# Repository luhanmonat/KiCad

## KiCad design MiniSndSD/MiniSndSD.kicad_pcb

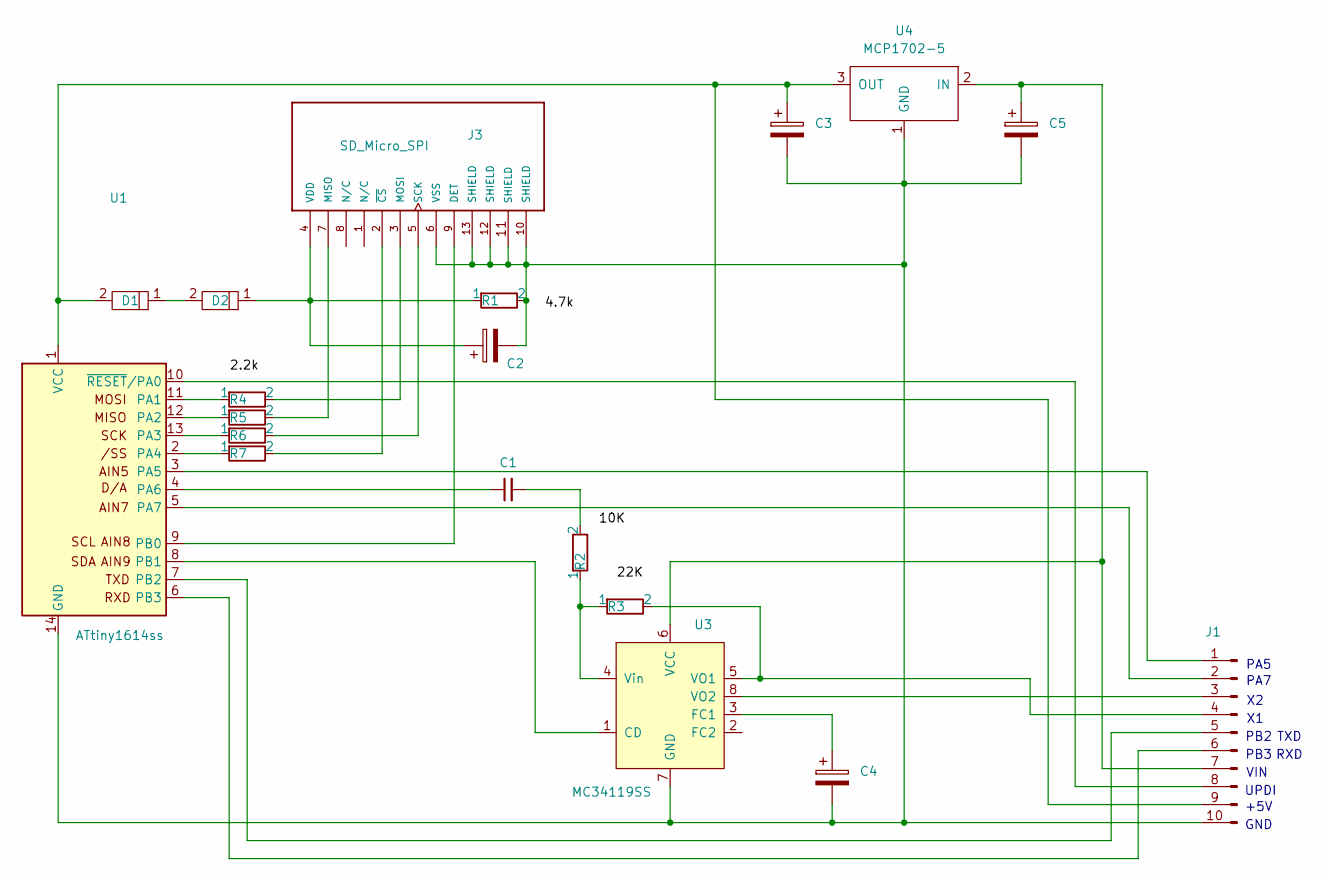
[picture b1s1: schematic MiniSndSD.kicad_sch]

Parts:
C1: C_Disc; C_Disc1
C2, C3, C4, C5: CP_Small; CP_Radial_D4.0mm_P2.00mm
D1, D2: 1N4004; DO_PWR
J1: Conn_01x10_MaleP; PinHeader_1x10_P2.54mm_Vertical
J3: SD_Micro_SPI; SD_Micro4A
R1, R2, R3, R4, R5, R6, R7: Resistor; QWSlim
U1: ATtiny1614ss; SOIC-14_3.9x8.7mm_P1.27mm
U3: MC34119SS; SOIC-8_3.9x4.9mm_P1.27mm
U4: MCP1702-5; TO-92X

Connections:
unnamed: C1.2, R2.2
unnamed: D1.1, D2.2
unnamed: J1.1, U1.3 (PA5)
unnamed: J1.2, U1.5 (PA7)
unnamed: J1.3, U3.8 (VO2)
unnamed: J1.4, R3.2, U3.5 (VO1)
unnamed: J1.5, U1.7 (PB2)
unnamed: J1.6, U1.6 (PB3)
unnamed: C5.1, J1.7, U3.6 (VCC), U4.2 (IN)
unnamed: J1.8, U1.10 (~RESET/PA0)
unnamed: C3.1, D1.2, J1.9, U1.1 (VCC), U4.3 (OUT)
unnamed: C2.2, C3.2, C4.2, C5.2, J1.10, J3.6 (VSS), J3.10 (SHIELD), J3.11 (SHIELD), J3.12 (SHIELD), J3.13 (SHIELD), R1.2, U1.14 (GND), U3.7 (GND), U4.1 (GND)
unnamed: J3.9 (DET), U1.9 (PB0)
unnamed: J3.7 (MISO), R5.2
unnamed: J3.3 (MOSI), R4.2
unnamed: J3.5 (SCK), R6.2
unnamed: C2.1, D2.1, J3.4 (VDD), R1.1
unnamed: J3.2 (~CS), R7.2
unnamed: R4.1, U1.11 (PA1)
unnamed: R5.1, U1.12 (PA2)
unnamed: R6.1, U1.13 (PA3)
unnamed: R7.1, U1.2 (PA4)
unnamed: C1.1, U1.4 (PA6)
unnamed: U1.8 (PB1), U3.1 (CD)
unnamed: C4.1, U3.3 (FC1)
unnamed: R2.1, R3.1, U3.4 (Vin)

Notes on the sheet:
RXD
PA7
PB2
TXD
UPDI
GND
+5V
PB3
PA5
VIN

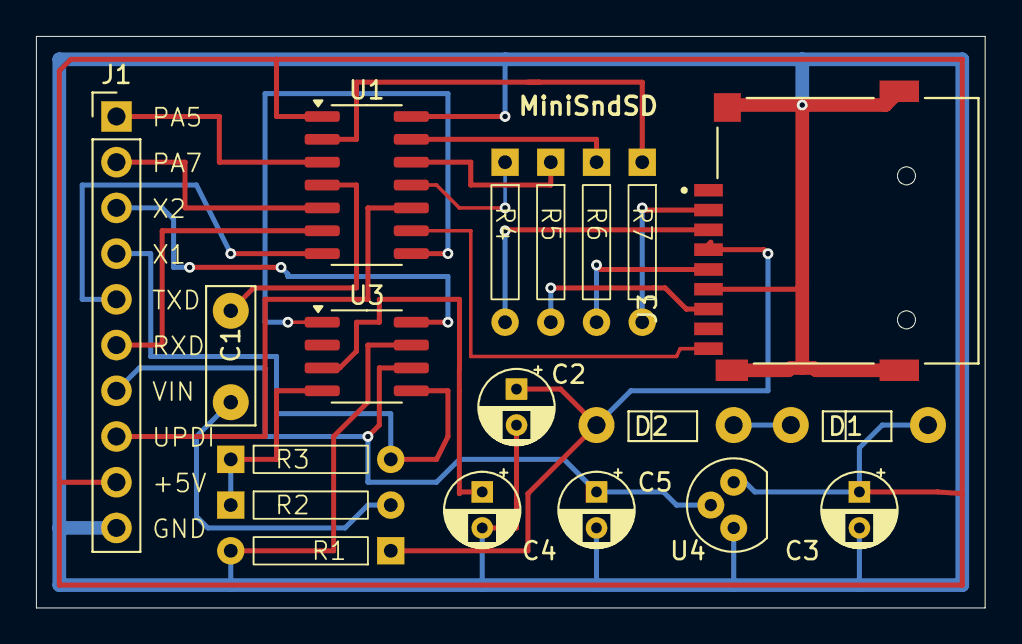
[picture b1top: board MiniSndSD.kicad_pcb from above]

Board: 2 copper layers, 52.7 x 31.7 mm, 19 parts (0 on the bottom side), 26 nets.

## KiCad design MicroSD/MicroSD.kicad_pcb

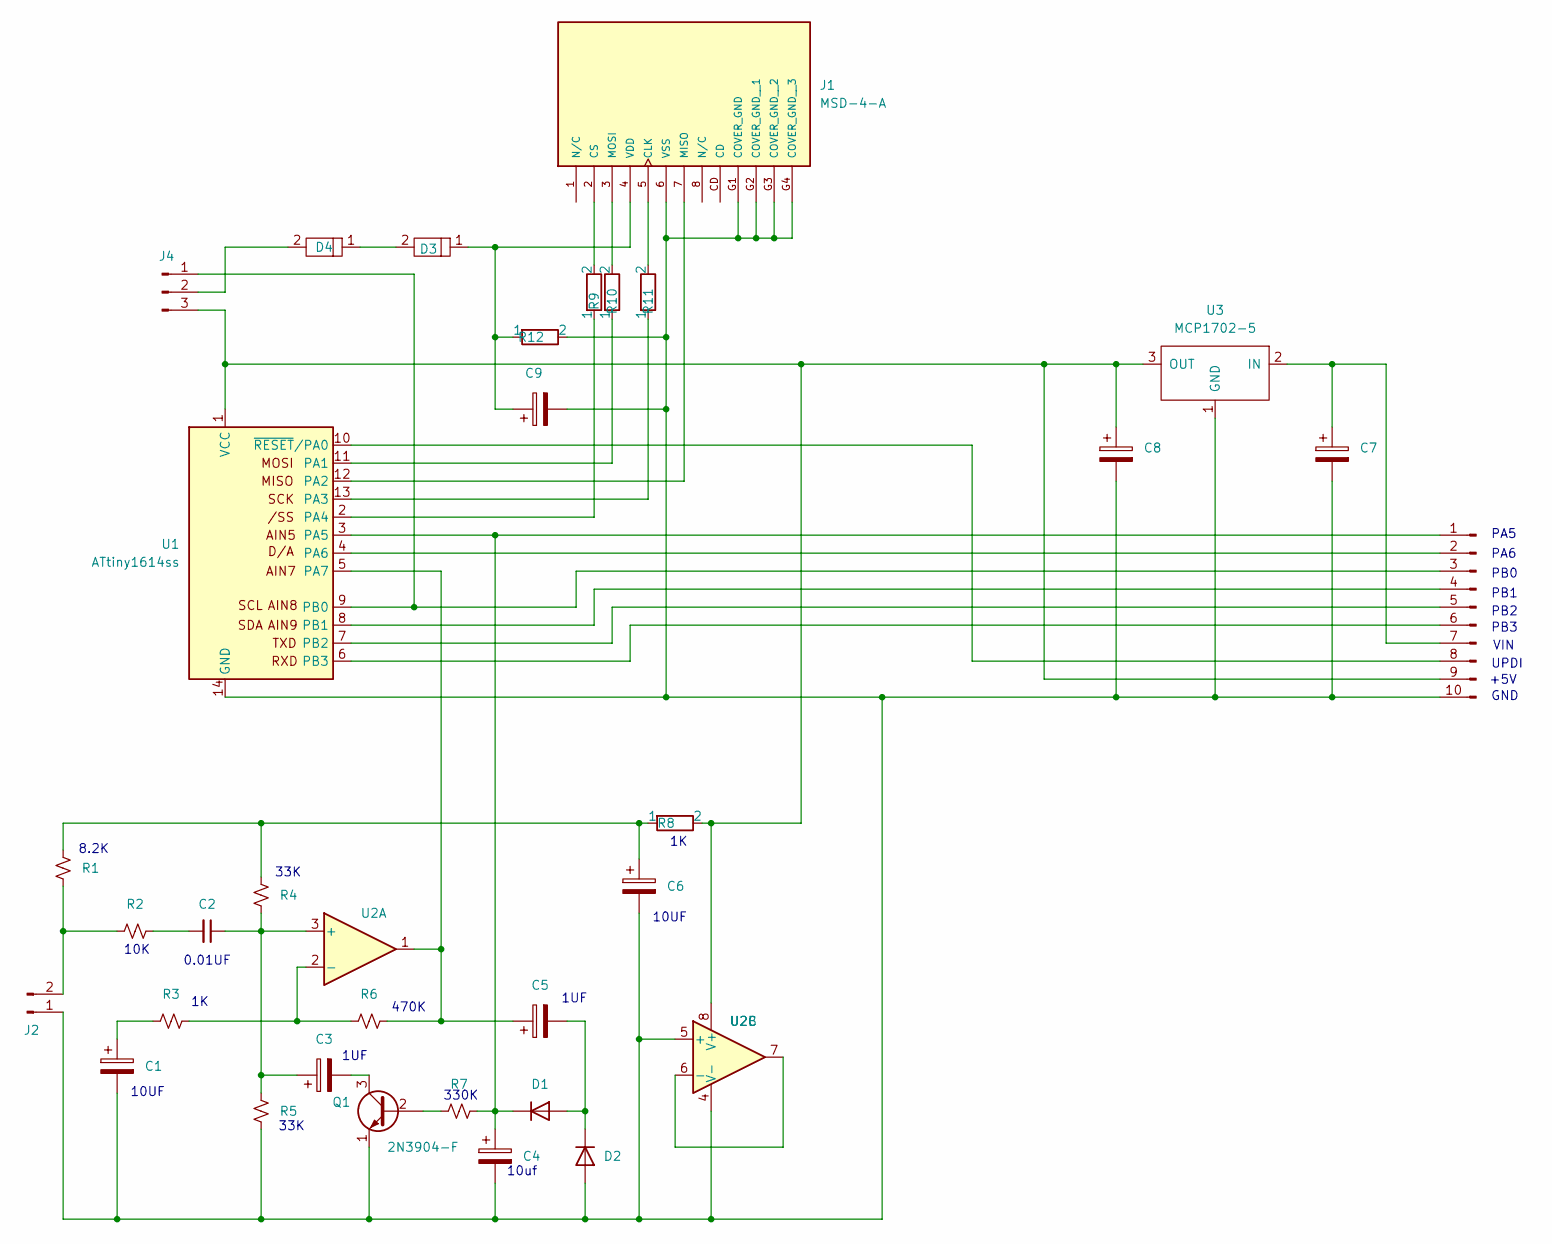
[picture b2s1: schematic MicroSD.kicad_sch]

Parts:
C1, C3, C4, C5, C6, C7, C8, C9: CP_Small; CP_Radial_D4.0mm_P2.00mm
C2: C_Disc; C_Disc1
D1, D2: 1N914; D_DO-35_SOD27_P7.62mm_Horizontal
D3, D4: 1N4004; DO_PWR
J1: MSD-4-A; CUI_MSD-4-A; PARTREV 1.0
J2: Conn_01x02_MH; PinHeader_1x02_P2.54mm_Horizontal
J3: Conn_01x10_MalePH; PinHeader_1x10_P2.54mm_Horizontal
J4: Conn_01x03_Pin; PinHeader_1x03_P2.54mm_Vertical
Q1: 2N3904-F; TO-92L_HandSolder
R1, R2, R3, R4, R5, R6, R7: R_Small; R_Qwatt
R8, R9, R10, R11, R12: Resistor; QWSlim
U1: ATtiny1614ss; SOIC-14_3.9x8.7mm_P1.27mm
U2: OpAmpDual; DIP-8_W7.62mm
U3: MCP1702-5; TO-92X

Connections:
unnamed: C1.1, R3.2
unnamed: C2.2, R2.1
unnamed: C6.1, R1.1, R4.1, R8.1
unnamed: C5.2, D1.2 (A), D2.1 (K)
unnamed: C4.1, D1.1 (K), J3.1, R7.1, U1.3 (PA5)
unnamed: C1.2, C4.2, C6.2, C7.2, C8.2, C9.2, D2.2 (A), J1.6 (VSS), J1.G1 (COVER_GND), J1.G2 (COVER_GND__1), J1.G3 (COVER_GND__2), J1.G4 (COVER_GND__3), J2.1, J3.10, Q1.1 (E), R5.2, R12.2, U1.14 (GND), U2.4 (V-), U2.5 (+), U3.1 (GND)
unnamed: D3.2, D4.1
unnamed: J1.5 (CLK), R11.2
unnamed: J1.2 (CS), R9.2
unnamed: J1.7 (MISO), U1.12 (PA2)
unnamed: J1.3 (MOSI), R10.2
unnamed: C9.1, D3.1, J1.4 (VDD), R12.1
unnamed: J2.2, R1.2, R2.2
unnamed: J3.2, U1.4 (PA6)
unnamed: J3.3, J4.1, U1.9 (PB0)
unnamed: J3.4, U1.8 (PB1)
unnamed: J3.5, U1.7 (PB2)
unnamed: J3.6, U1.6 (PB3)
unnamed: C7.1, J3.7, U3.2 (IN)
unnamed: J3.8, U1.10 (~RESET/PA0)
unnamed: C8.1, J3.9, J4.3, R8.2, U1.1 (VCC), U2.8 (V+), U3.3 (OUT)
unnamed: D4.2, J4.2
unnamed: Q1.2 (B), R7.2
unnamed: C3.2, Q1.3 (C)
unnamed: R10.1, U1.11 (PA1)
unnamed: R11.1, U1.13 (PA3)
unnamed: R9.1, U1.2 (PA4)
unnamed: C5.1, R6.1, U1.5 (PA7), U2.1
unnamed: C2.1, C3.1, R4.2, R5.1, U2.3 (+)
unnamed: R3.1, R6.2, U2.2 (-)
unnamed: U2.6 (-), U2.7

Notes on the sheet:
+5V
10K
UPDI
0.01UF
PB2
470K
PA5
GND
PB1
PB3
PB0
10UF
PA6
33K
1UF
10uf
330K
VIN
8.2K

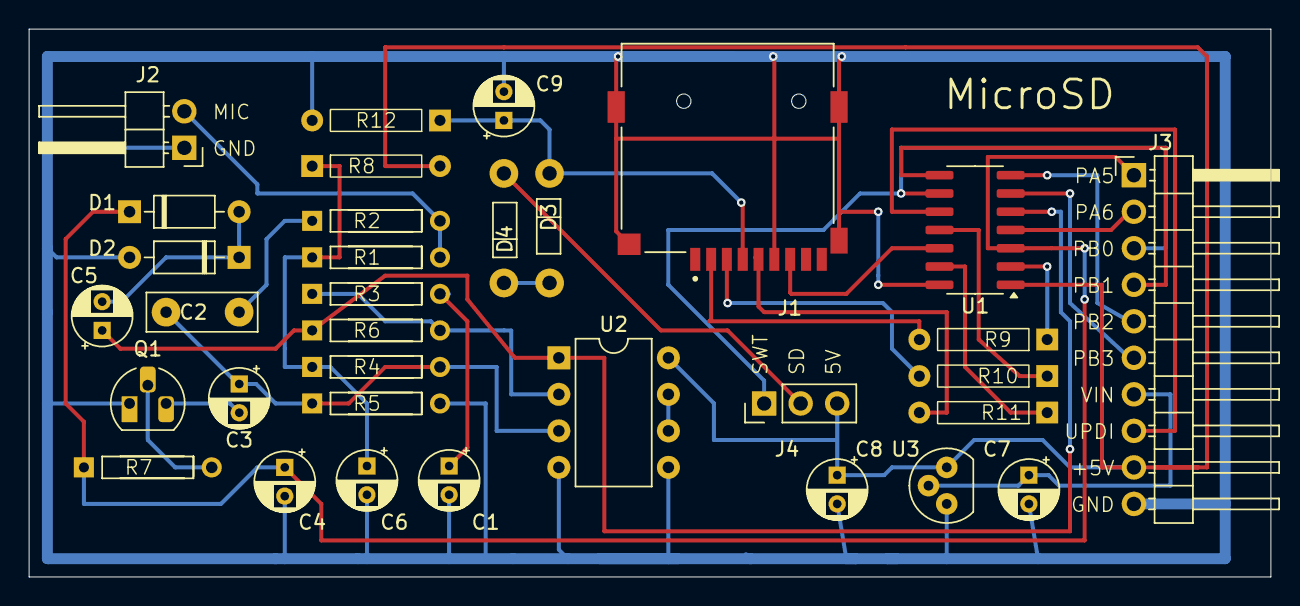
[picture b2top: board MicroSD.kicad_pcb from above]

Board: 2 copper layers, 86.4 x 38.1 mm, 33 parts (0 on the bottom side), 31 nets.

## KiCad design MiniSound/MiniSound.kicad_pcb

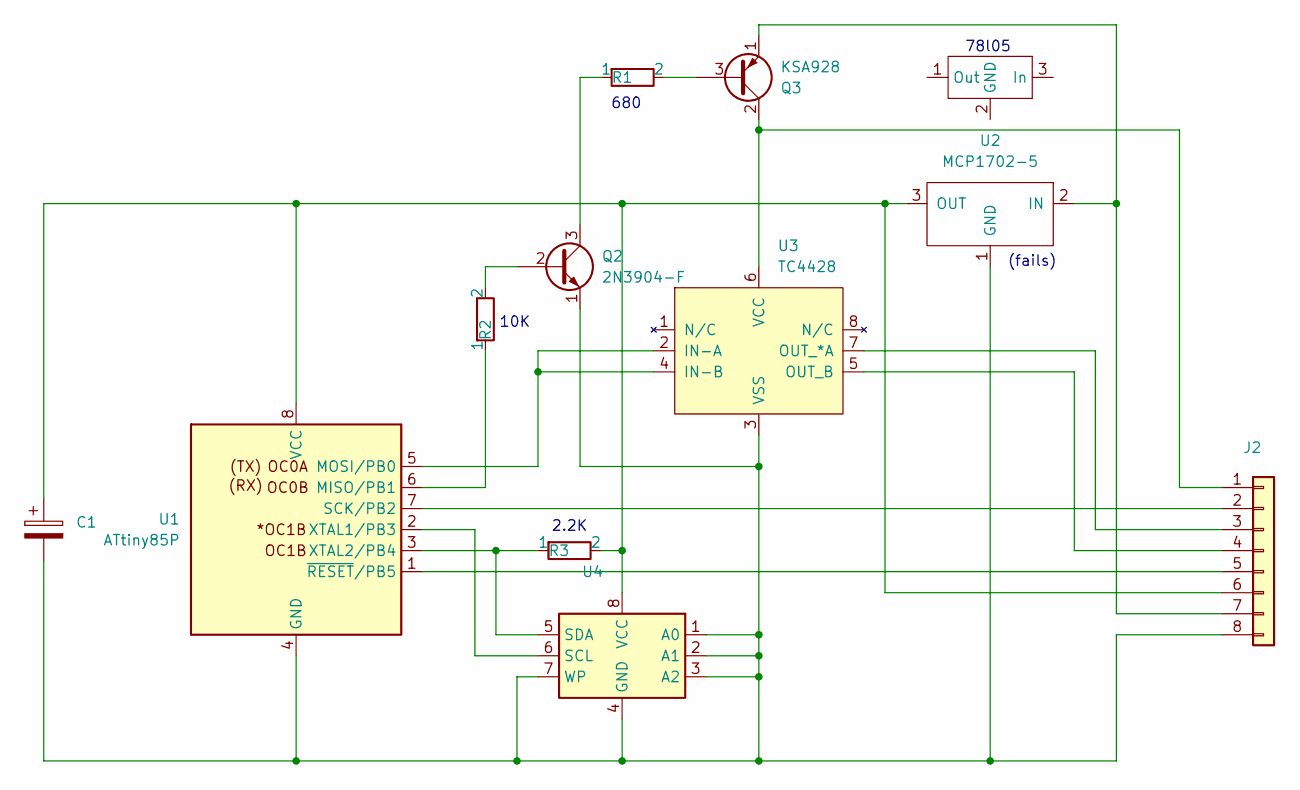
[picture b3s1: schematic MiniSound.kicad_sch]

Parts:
C1: CP_Small; CP_Radial_D4.0mm_P2.00mm
J2: Conn_01x08_H; PinHeader_1x08_P2.54mm_Horizontal
Q2: 2N3904-F; TO-92X
Q3: KSA928; TO-92X
R1, R2, R3: Resistor; QWSlim
U1: ATtiny85P; DIP-8_W7.62mm
U2: MCP1702-5; TO-92X
U3: TC4428; DIP-8_W7.62mm_LongPads
U4: 24LC512P; DIP-8_W_7.62mm
U5: (no value)

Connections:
unnamed: J2.1, Q3.2 (C), U3.6 (VCC)
unnamed: J2.2, U1.7 (SCK/PB2)
unnamed: J2.3, U3.7 (OUT_*A)
unnamed: J2.4, U3.5 (OUT_B)
unnamed: J2.5, U1.1 (~RESET/PB5)
unnamed: C1.1, J2.6, R3.2, U1.8 (VCC), U2.3 (OUT), U4.8 (VCC)
unnamed: J2.7, Q3.1 (E), U2.2 (IN)
unnamed: C1.2, J2.8, Q2.1 (E), U1.4 (GND), U2.1 (GND), U3.3 (VSS), U4.1 (A0), U4.2 (A1), U4.3 (A2), U4.4 (GND), U4.7 (WP)
unnamed: Q2.2 (B), R2.2
unnamed: Q2.3 (C), R1.1
unnamed: Q3.3 (B), R1.2
unnamed: R2.1, U1.6 (MISO/PB1)
unnamed: U1.5 (MOSI/PB0), U3.2 (IN-A), U3.4 (IN-B)
unnamed: U1.2 (XTAL1/PB3), U4.6 (SCL)
unnamed: R3.1, U1.3 (XTAL2/PB4), U4.5 (SDA)

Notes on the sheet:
10K
78l05
680
(fails)
2.2K

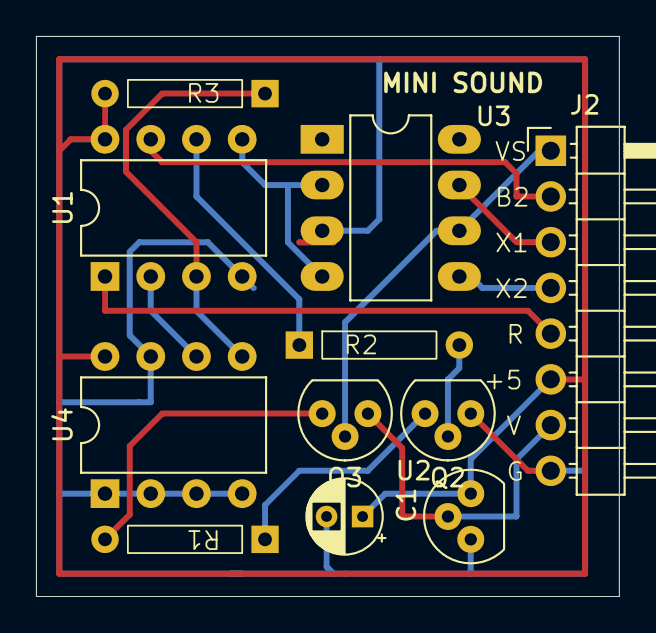
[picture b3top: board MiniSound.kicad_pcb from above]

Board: 2 copper layers, 32.4 x 31.1 mm, 11 parts (0 on the bottom side), 15 nets.

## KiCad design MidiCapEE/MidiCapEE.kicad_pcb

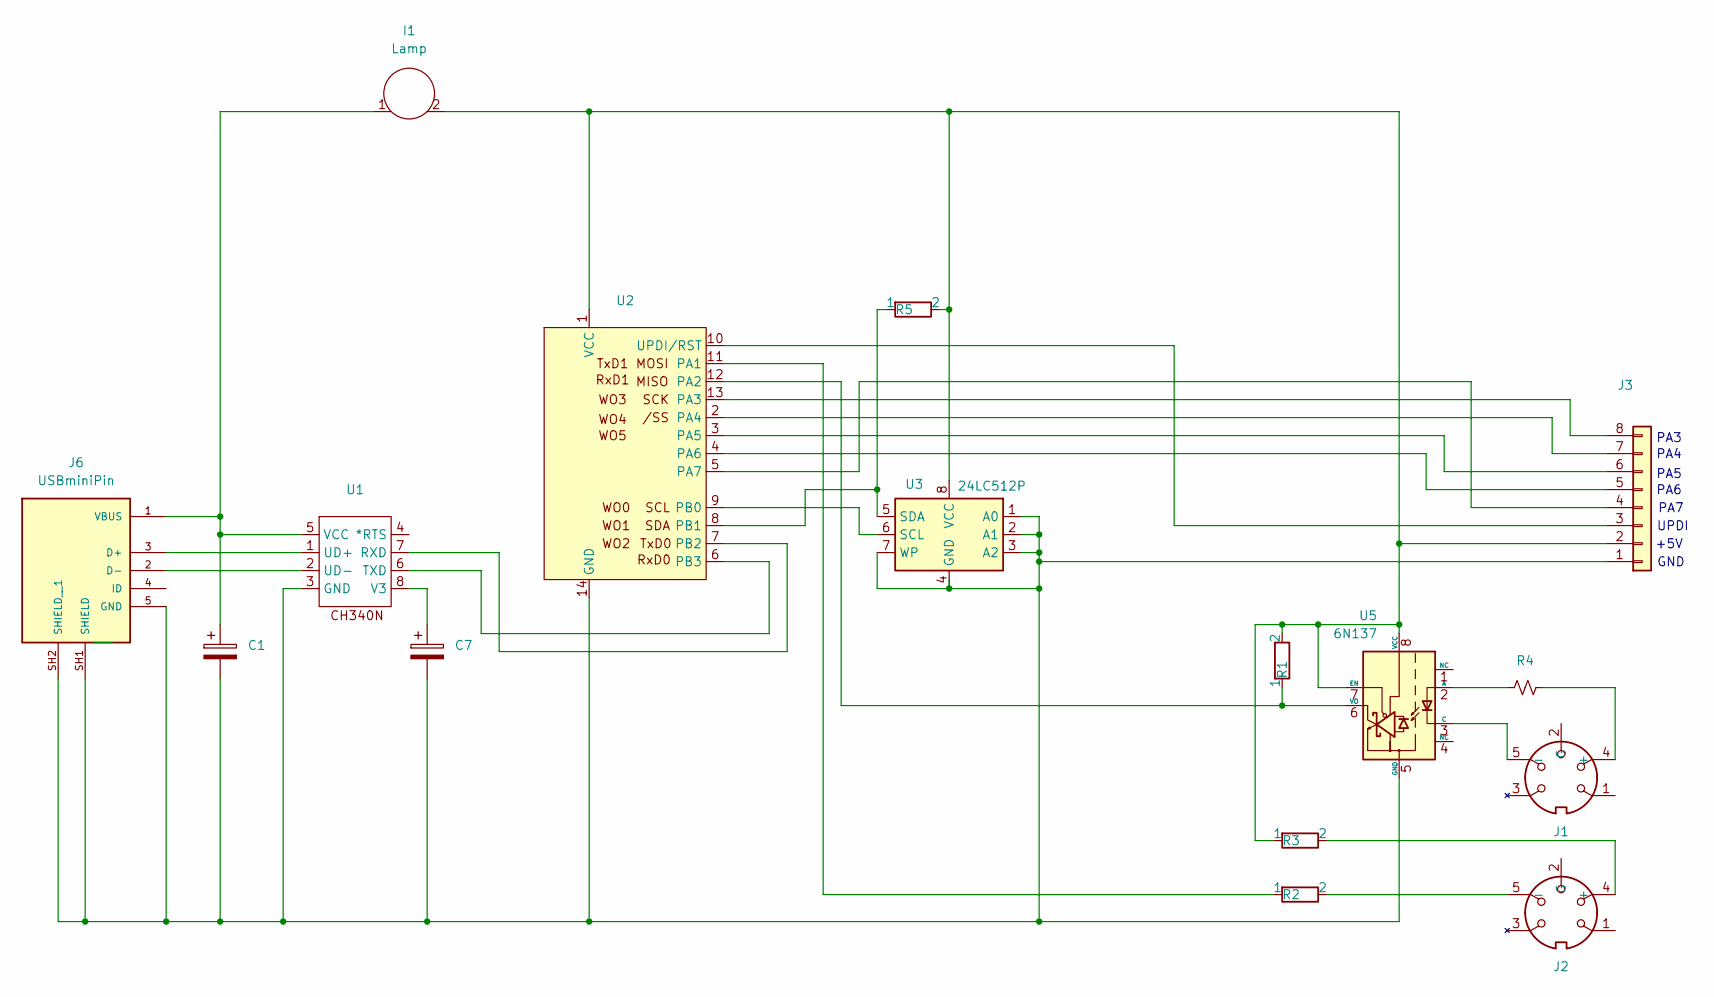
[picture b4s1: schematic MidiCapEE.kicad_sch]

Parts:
C1, C7: CP_Small; CP_Radial_D4.0mm_P2.00mm
I1: Lamp; Lamp1
J1, J2: Midi-5; Din5PCB
J3: Conn_01x08_H; PinHeader_1x08_P2.54mm_Horizontal
J6: USBminiPin; PARTREV A1
R1, R2, R3, R5: Resistor; QWSlim
R4: R_Small; R_Qwatt
U1: SOIC-8_3.9x4.9mm_P1.27mm
U2: SOIC-14_3.9x8.7mm_P1.27mm
U3: 24LC512P; DIP-8_W_7.62mm
U5: 6N137; DIP-8_W7.62mm

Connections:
unnamed: J1.4 (+), R4.1
unnamed: J1.5 (-), U5.3 (C)
unnamed: J2.4 (+), R3.2
unnamed: J2.5 (-), R2.2
unnamed: C1.2, C7.2, J3.1, J6.5 (GND), J6.SH1 (SHIELD), J6.SH2 (SHIELD__1), U1.3 (GND), U2.14 (GND), U3.1 (A0), U3.2 (A1), U3.3 (A2), U3.4 (GND), U3.7 (WP), U5.5 (GND)
unnamed: I1.2, J3.2, R1.2, R3.1, R5.2, U2.1 (VCC), U3.8 (VCC), U5.7 (EN), U5.8 (VCC)
unnamed: J3.3, U2.10 (UPDI/RST)
unnamed: J3.4, U2.5 (PA7)
unnamed: J3.5, U2.4 (PA6)
unnamed: J3.6, U2.3 (PA5)
unnamed: J3.7, U2.2 (PA4)
unnamed: J3.8, U2.13 (PA3)
unnamed: J6.3 (D+), U1.1 (UD+)
unnamed: J6.2 (D-), U1.2 (UD-)
unnamed: C1.1, I1.1, J6.1 (VBUS), U1.5 (VCC)
unnamed: U1.7 (RXD), U2.7 (PB2)
unnamed: U1.6 (TXD), U2.6 (PB3)
unnamed: C7.1, U1.8 (V3)
unnamed: R2.1, U2.11 (PA1)
unnamed: R1.1, U2.12 (PA2), U5.6 (VO)
unnamed: U2.9 (PB0), U3.6 (SCL)
unnamed: R5.1, U2.8 (PB1), U3.5 (SDA)
unnamed: R4.2, U5.2 (A)

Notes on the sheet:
UPDI
GND
PA3
PA7
+5V
PA6
PA4
PA5

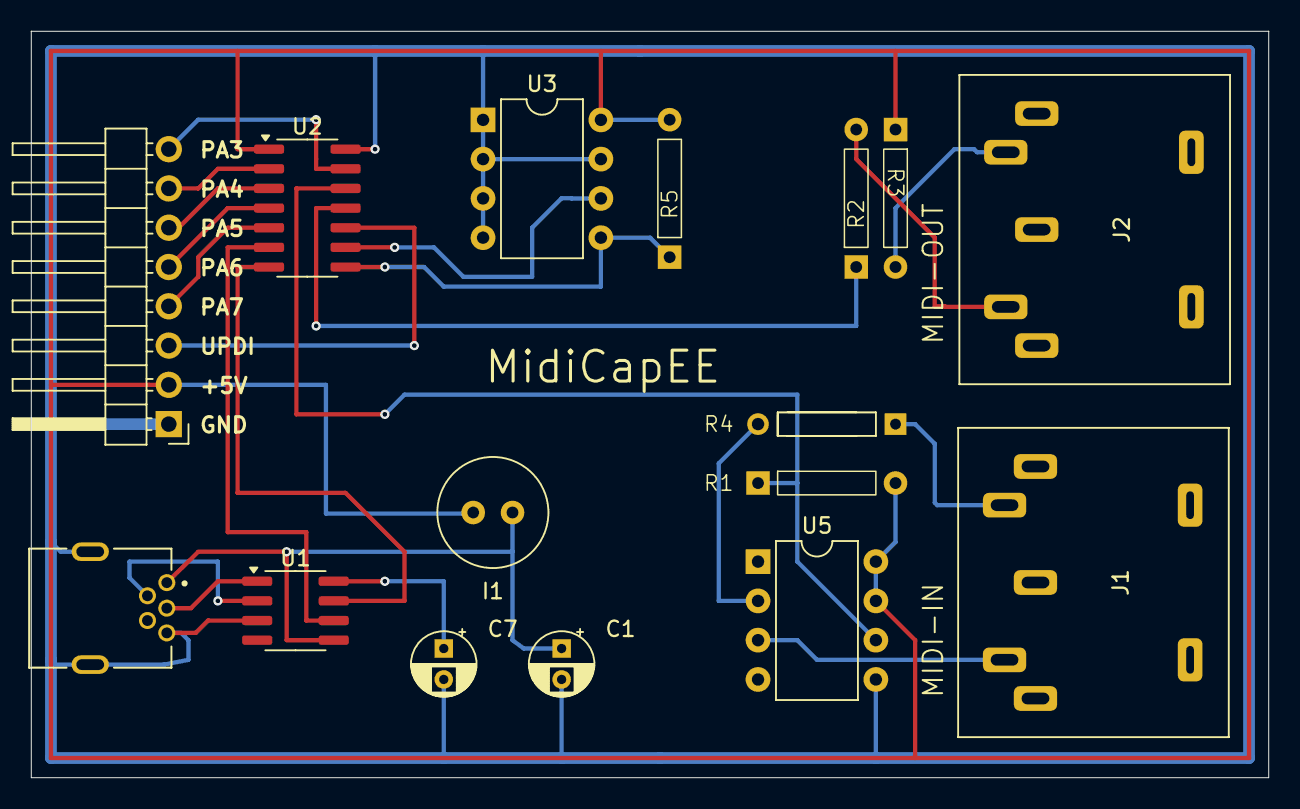
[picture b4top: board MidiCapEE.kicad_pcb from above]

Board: 2 copper layers, 80.0 x 48.3 mm, 16 parts (0 on the bottom side), 23 nets.

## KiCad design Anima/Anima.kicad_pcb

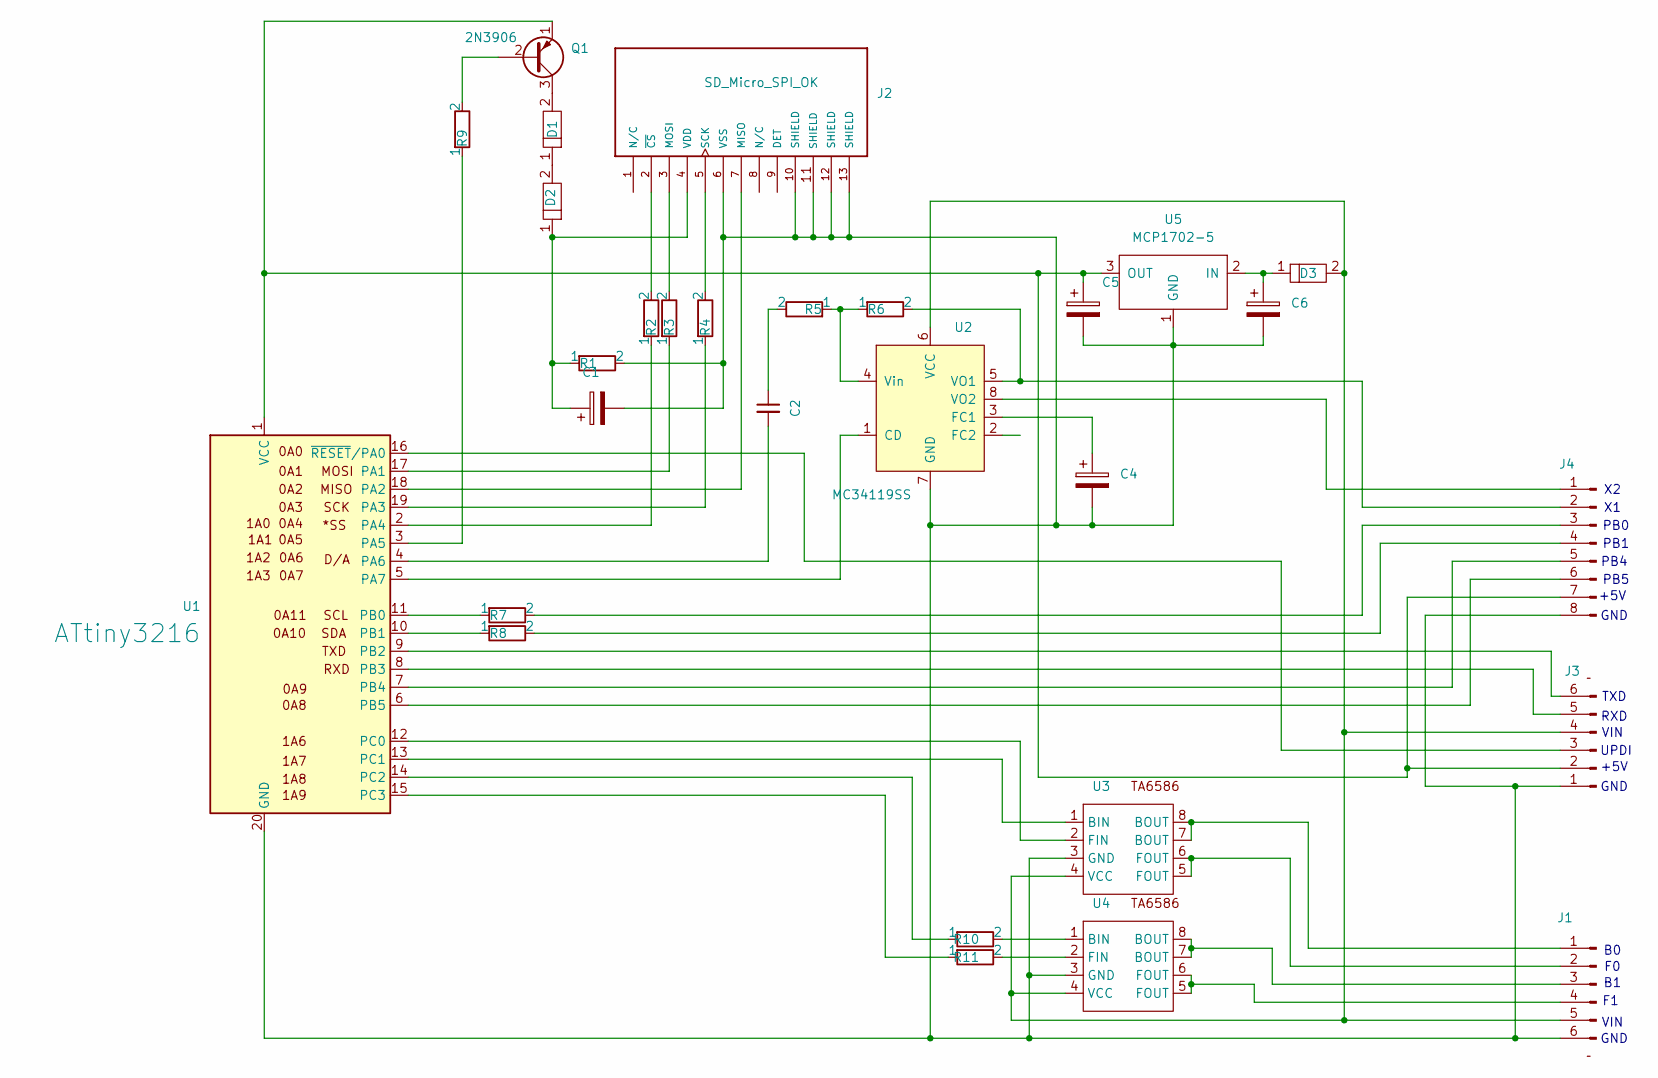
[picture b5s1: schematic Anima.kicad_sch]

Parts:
C1, C4, C5: CP_Small; CP_Radial_D4.0mm_P2.00mm
C2: C_Disc; C_Disc1
C6: CP_Med; CP_Radial_D6.3mm_P2.50mm
D1, D2, D3: 1N4004; DO_PWR
J1: Conn_1x6_M; Foot1x6
J2: SD_Micro_SPI_OK; SD_Micro4A
J3: Conn_01x06_F; PinHeader_1x06_P2.54mm_Horizontal
J4: PinHeader_1x08_P2.54mm_Horizontal
Q1: 2N3906; TO-92X
R1, R2, R3, R4, R5, R6, R7, R8, R9, R10, R11: Resistor; QWSlim
U1: ATtiny3216; DIP-20_3216
U2: MC34119SS; SOIC-8_3.9x4.9mm_P1.27mm
U3, U4: DIP-8_Socket
U5: MCP1702-5; TO-92X

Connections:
unnamed: C2.1, R5.2
unnamed: D1.1, D2.2
unnamed: J1.1, U3.7 (BOUT), U3.8 (BOUT)
unnamed: J1.2, U3.5 (FOUT), U3.6 (FOUT)
unnamed: J1.3, U4.7 (BOUT), U4.8 (BOUT)
unnamed: J1.4, U4.5 (FOUT), U4.6 (FOUT)
unnamed: D3.2, J1.5, J3.4, U2.6 (VCC), U3.4 (VCC), U4.4 (VCC)
unnamed: C1.2, C4.2, C5.2, C6.2, J1.6, J2.6 (VSS), J2.10 (SHIELD), J2.11 (SHIELD), J2.12 (SHIELD), J2.13 (SHIELD), J3.1, J4.8, R1.2, U1.20 (GND), U2.7 (GND), U3.3 (GND), U4.3 (GND), U5.1 (GND)
unnamed: J2.7 (MISO), U1.18 (PA2)
unnamed: J2.3 (MOSI), R3.2
unnamed: J2.5 (SCK), R4.2
unnamed: C1.1, D2.1, J2.4 (VDD), R1.1
unnamed: J2.2 (~CS), R2.2
unnamed: C5.1, J3.2, J4.7, Q1.1 (E), U1.1 (VCC), U5.3 (OUT)
unnamed: J3.3, U1.16 (~RESET/PA0)
unnamed: J3.5, U1.8 (PB3)
unnamed: J3.6, U1.9 (PB2)
unnamed: J4.1, U2.8 (VO2)
unnamed: J4.2, R6.2, U2.5 (VO1)
unnamed: J4.3, R7.2
unnamed: J4.4, R8.2
unnamed: J4.5, U1.7 (PB4)
unnamed: J4.6, U1.6 (PB5)
unnamed: Q1.2 (B), R9.2
unnamed: D1.2, Q1.3 (C)
unnamed: R3.1, U1.17 (PA1)
unnamed: R4.1, U1.19 (PA3)
unnamed: R2.1, U1.2 (PA4)
unnamed: R9.1, U1.3 (PA5)
unnamed: C2.2, U1.4 (PA6)
unnamed: U1.5 (PA7), U2.1 (CD)
unnamed: R7.1, U1.11 (PB0)
unnamed: R8.1, U1.10 (PB1)
unnamed: U1.12 (PC0), U3.2 (FIN)
unnamed: U1.13 (PC1), U3.1 (BIN)
unnamed: R10.1, U1.14 (PC2)
unnamed: R11.1, U1.15 (PC3)
unnamed: C4.1, U2.3 (FC1)
unnamed: R5.1, R6.1, U2.4 (Vin)
unnamed: R10.2, U4.1 (BIN)
unnamed: R11.2, U4.2 (FIN)
unnamed: C6.1, D3.1, U5.2 (IN)

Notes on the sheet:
GND
PB5
+5V
VIN
TXD
RXD
PB1
PB4
UPDI
PB0

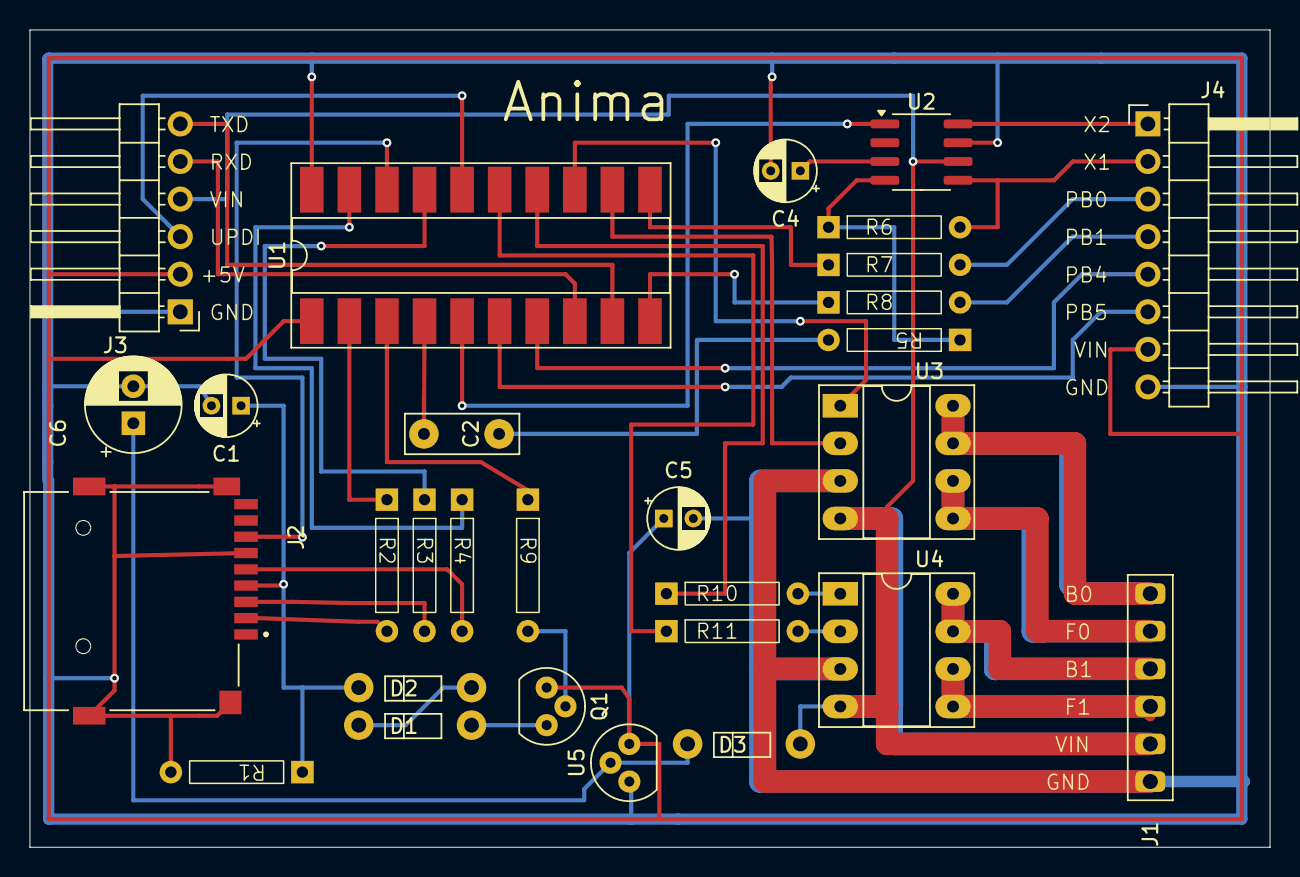
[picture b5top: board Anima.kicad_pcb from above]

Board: 2 copper layers, 83.8 x 55.2 mm, 29 parts (0 on the bottom side), 42 nets.

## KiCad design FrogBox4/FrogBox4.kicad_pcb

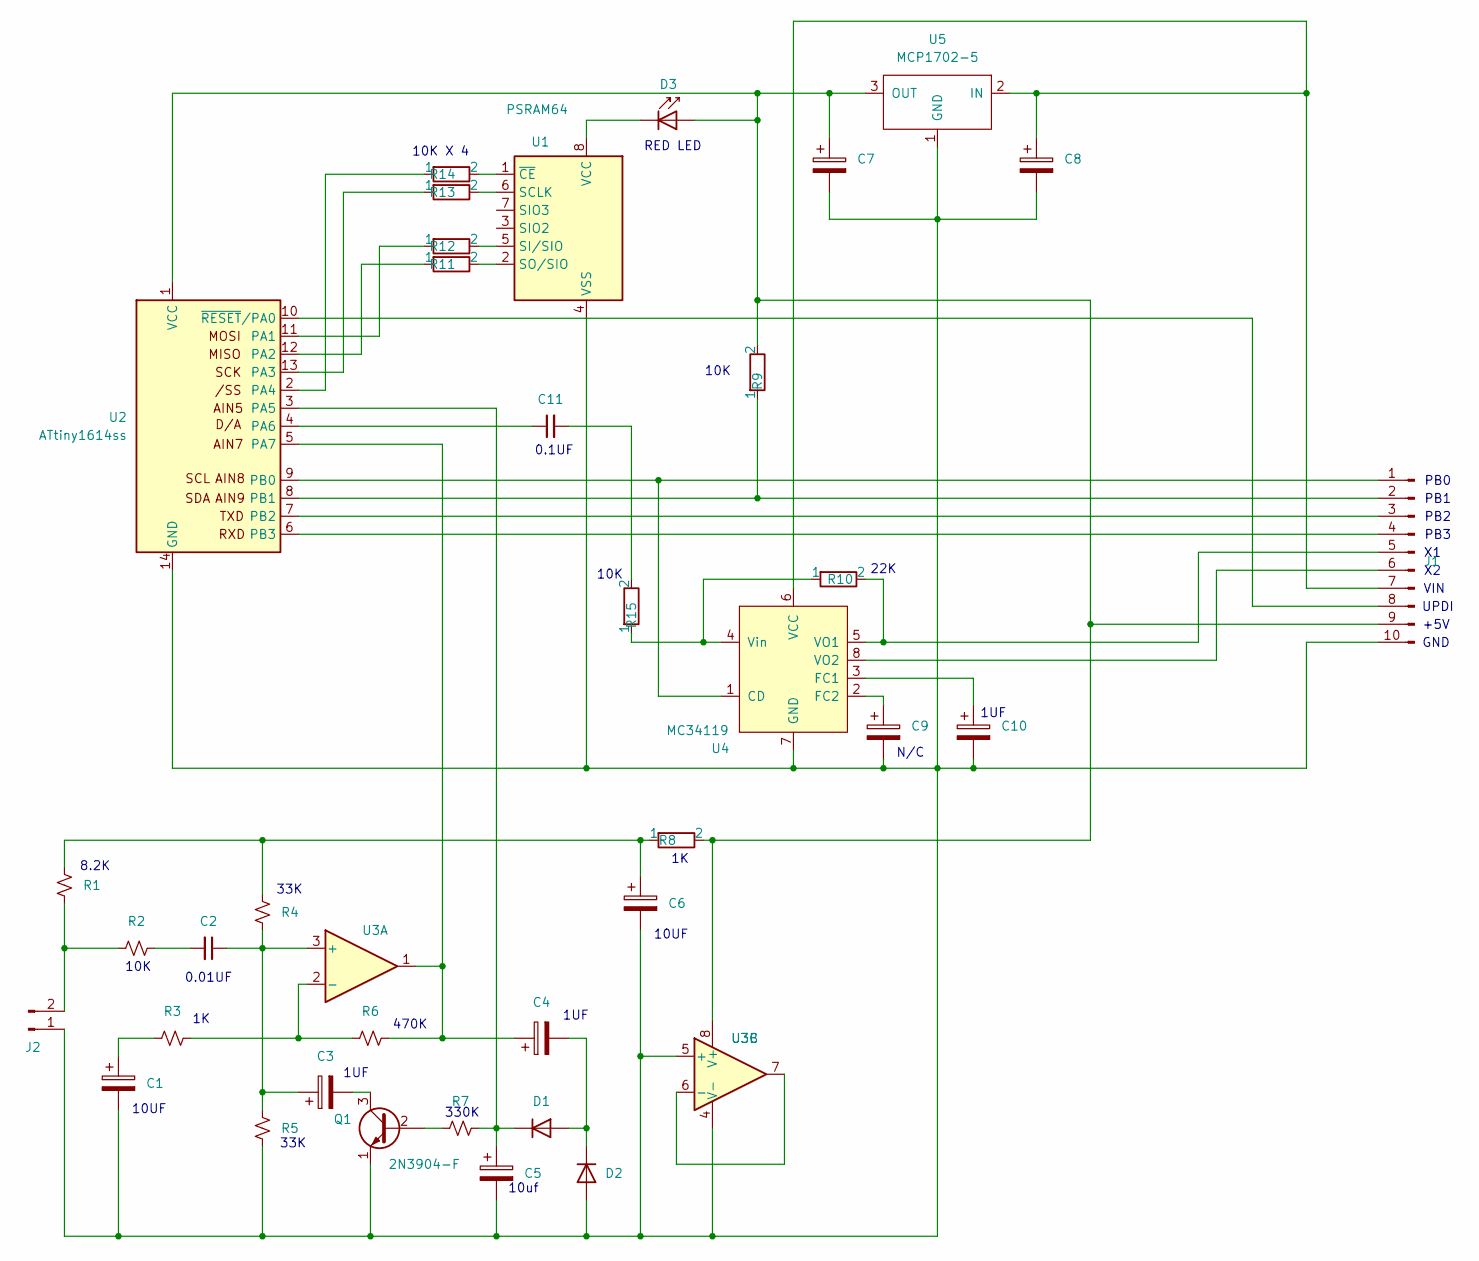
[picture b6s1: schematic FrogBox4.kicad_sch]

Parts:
C1, C3, C4, C5, C6, C7, C8, C9, C10: CP_Small; CP_Radial_D4.0mm_P2.00mm
C2, C11: C_Disc; C_Disc1
D1, D2: 1N914; D_DO-35_SOD27_P7.62mm_Horizontal
D3: LED_5mm; LED_D5.0mm_IRGrey
J1: Conn_01x10_MalePH; PinHeader_1x10_P2.54mm_Horizontal
J2: Conn_01x02_MH; PinHeader_1x02_P2.54mm_Horizontal
Q1: 2N3904-F; TO-92L_HandSolder
R1, R2, R3, R4, R5, R6, R7: R_Small; R_Qwatt
R8, R9, R10, R11, R12, R13, R14, R15: Resistor; QWSlim
U1: PSRAM64; SOIC-8_3.9x4.9mm_P1.27mm
U2: ATtiny1614ss; SOIC-14_3.9x8.7mm_P1.27mm
U3: OpAmpDual; DIP-8_W7.62mm
U4: MC34119; DIP-8_W7.62mm
U5: MCP1702-5; TO-92X

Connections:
unnamed: C1.1, R3.2
unnamed: C2.2, R2.1
unnamed: C6.1, R1.1, R4.1, R8.1
unnamed: C11.2, R15.2
unnamed: C4.2, D1.2 (A), D2.1 (K)
unnamed: C5.1, D1.1 (K), R7.1, U2.3 (PA5)
unnamed: C1.2, C5.2, C6.2, C7.2, C8.2, C9.2, C10.2, D2.2 (A), J1.10, J2.1, Q1.1 (E), R5.2, U1.4 (VSS), U2.14 (GND), U3.4 (V-), U3.5 (+), U4.7 (GND), U5.1 (GND)
unnamed: C7.1, D3.2 (A), J1.9, R8.2, R9.2, U2.1 (VCC), U3.8 (V+), U5.3 (OUT)
unnamed: D3.1 (K), U1.8 (VCC)
unnamed: J1.1, U2.9 (PB0), U4.1 (CD)
unnamed: J1.2, R9.1, U2.8 (PB1)
unnamed: J1.3, U2.7 (PB2)
unnamed: J1.4, U2.6 (PB3)
unnamed: J1.5, R10.2, U4.5 (VO1)
unnamed: J1.6, U4.8 (VO2)
unnamed: C8.1, J1.7, U4.6 (VCC), U5.2 (IN)
unnamed: J1.8, U2.10 (~RESET/PA0)
unnamed: J2.2, R1.2, R2.2
unnamed: Q1.2 (B), R7.2
unnamed: C3.2, Q1.3 (C)
unnamed: R13.2, U1.6 (SCLK)
unnamed: R12.2, U1.5 (SI/SIO)
unnamed: R11.2, U1.2 (SO/SIO)
unnamed: R14.2, U1.1 (~CE)
unnamed: R12.1, U2.11 (PA1)
unnamed: R11.1, U2.12 (PA2)
unnamed: R13.1, U2.13 (PA3)
unnamed: R14.1, U2.2 (PA4)
unnamed: C11.1, U2.4 (PA6)
unnamed: C4.1, R6.1, U2.5 (PA7), U3.1
unnamed: C2.1, C3.1, R4.2, R5.1, U3.3 (+)
unnamed: R3.1, R6.2, U3.2 (-)
unnamed: U3.6 (-), U3.7
unnamed: C10.1, U4.3 (FC1)
unnamed: C9.1, U4.2 (FC2)
unnamed: R10.1, R15.1, U4.4 (Vin)

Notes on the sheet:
PB1
GND
10K X 4
UPDI
0.01UF
1UF
470K
PB2
PB0
0.1UF
PB3
+5V
10K
22K
33K
10UF
10uf
8.2K
VIN
N/C
RED LED
330K

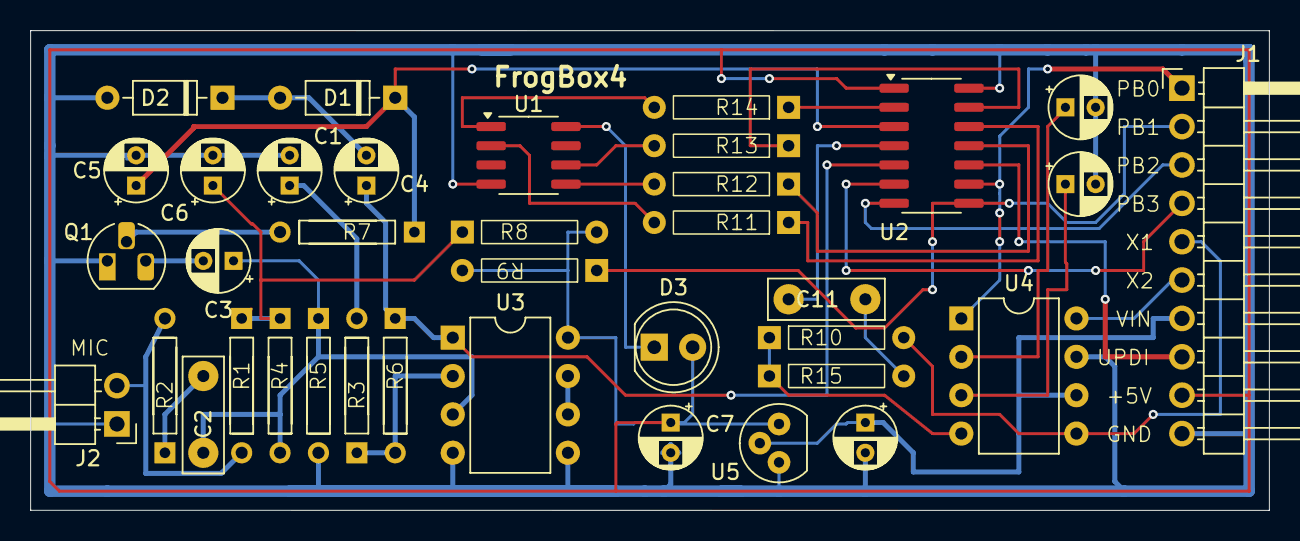
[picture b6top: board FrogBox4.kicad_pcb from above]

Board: 2 copper layers, 82.0 x 31.8 mm, 37 parts (0 on the bottom side), 36 nets.

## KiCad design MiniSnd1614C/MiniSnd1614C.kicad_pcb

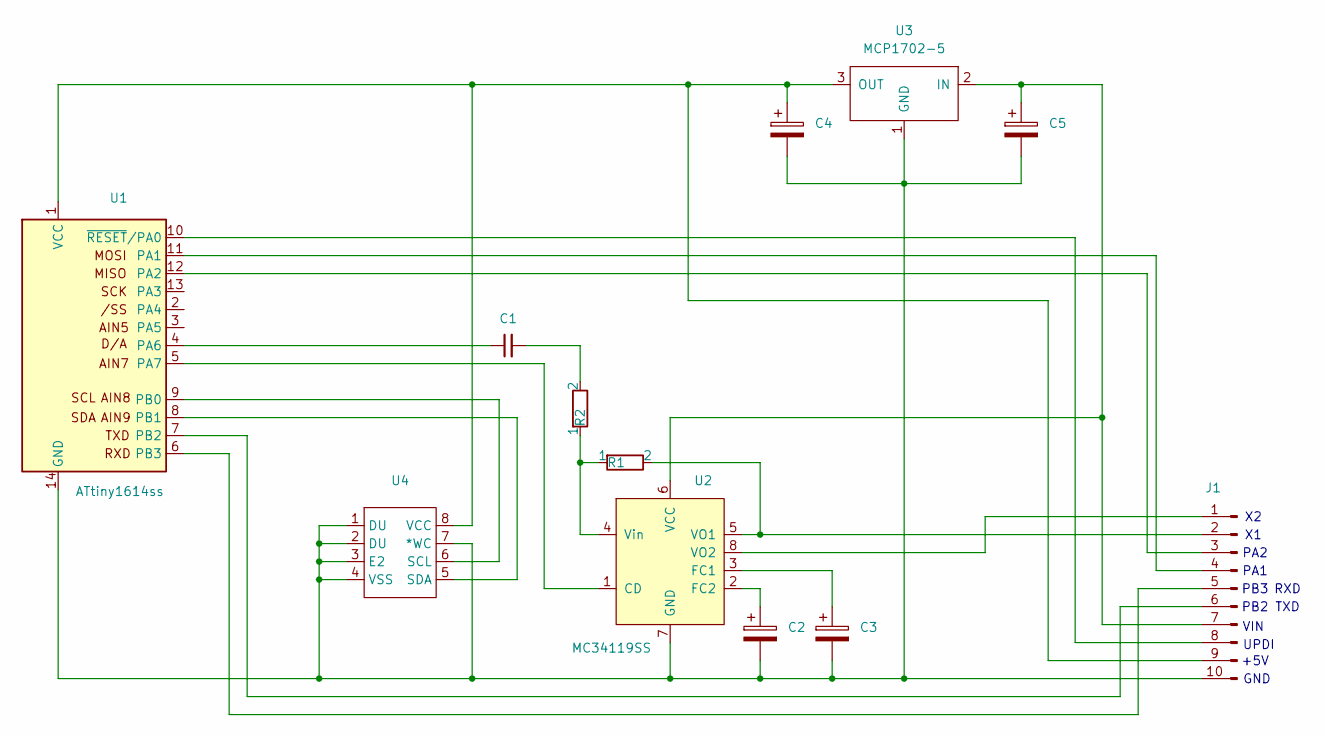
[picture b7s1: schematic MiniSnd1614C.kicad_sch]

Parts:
C1: C_Disc; C_Disc1
C2, C3, C4, C5: CP_Small; CP_Radial_D4.0mm_P2.00mm
J1: Conn_01x10_MaleP; PinHeader_1x10_P2.54mm_Vertical
R1, R2: Resistor; QWSlim
U1: ATtiny1614ss; SOIC-14_3.9x8.7mm_P1.27mm
U2: MC34119SS; SOIC-8_3.9x4.9mm_P1.27mm
U3: MCP1702-5; TO-92X
U4: SOIC-8-L

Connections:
unnamed: C1.2, R2.2
unnamed: J1.1, U2.8 (VO2)
unnamed: J1.2, R1.2, U2.5 (VO1)
unnamed: J1.3, U1.12 (PA2)
unnamed: J1.4, U1.11 (PA1)
unnamed: J1.5, U1.6 (PB3)
unnamed: J1.6, U1.7 (PB2)
unnamed: C5.1, J1.7, U2.6 (VCC), U3.2 (IN)
unnamed: J1.8, U1.10 (~RESET/PA0)
unnamed: C4.1, J1.9, U1.1 (VCC), U3.3 (OUT), U4.8 (VCC)
unnamed: C2.2, C3.2, C4.2, C5.2, J1.10, U1.14 (GND), U2.7 (GND), U3.1 (GND), U4.1 (DU), U4.2 (DU), U4.3 (E2), U4.4 (VSS), U4.7 (*WC)
unnamed: C1.1, U1.4 (PA6)
unnamed: U1.5 (PA7), U2.1 (CD)
unnamed: U1.9 (PB0), U4.6 (SCL)
unnamed: U1.8 (PB1), U4.5 (SDA)
unnamed: C3.1, U2.3 (FC1)
unnamed: C2.1, U2.2 (FC2)
unnamed: R1.1, R2.1, U2.4 (Vin)

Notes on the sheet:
+5V
PA2
PB2
TXD
GND
UPDI
PB3
RXD
VIN
PA1

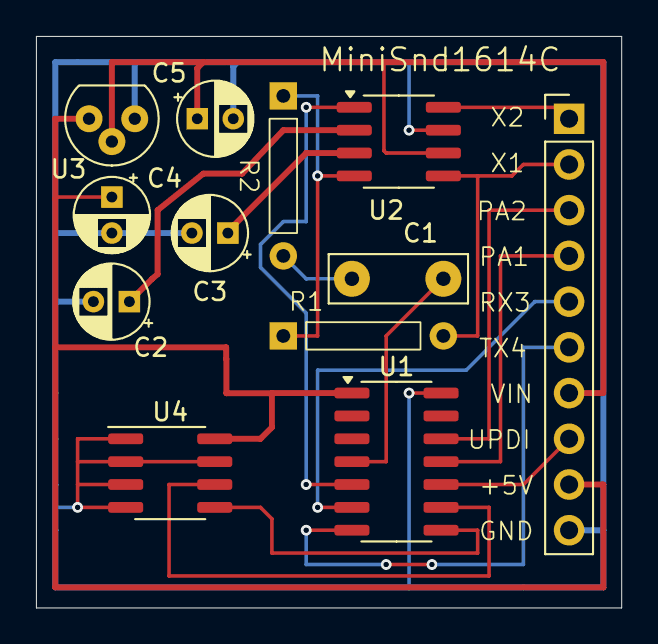
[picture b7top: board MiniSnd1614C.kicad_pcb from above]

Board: 2 copper layers, 32.5 x 31.8 mm, 12 parts (0 on the bottom side), 18 nets.
